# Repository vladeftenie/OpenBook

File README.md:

# OpenBook ESP32-C6 Complete Hardware Guide

## Overview
The OpenBook is an e-reader built around the ESP32-C6 chip. It uses an e-paper screen (like Kindle), has an SD card slot for books, can check room temperature and air quality, and has a battery that lasts a long time. It connects to Wi-Fi and Bluetooth so you can download books and update it.

## Main Parts

### Brain: ESP32-C6-WROOM-1-N8
- **What It Does**: Controls everything in the device
- **Architecture**: RISC-V (Single-Core)
- **Wireless**: Wi-Fi 6, Bluetooth 5 LE
- **Power Needs**: 3.3V
- **How It Talks**: SPI, I²C, UART, GPIO, USB

## Display Details

### E-Paper Screen
- **How It Connects**: SPI (shares wires with SD card)
- **Wires**:
  - Select Wire (EPD_CS): `GPIO 10`
  - Command Wire (EPD_DC): `GPIO 5`
  - Reset Wire: `GPIO 23`
  - Busy Signal: `GPIO 3`
  - Data Wires: shared with SD card
- **Screen Size**: 1404 × 1872 pixels (6.8")

## Memory Options

### SD Card Slot
- **How It Connects**: SPI
- **Wires**:
  - Select Wire (SS_SD): `GPIO 4`
  - Data Out (MOSI): `GPIO 7`
  - Data In (MISO): `GPIO 27`
  - Clock (SCK): `GPIO 6`
- **Space**: Works with cards up to 32GB

### Built-in Flash Memory (64MB)
- **How It Connects**: SPI (shared)
- **Wires**:
  - Select Wire (FLASH_CS): `GPIO 12`
  - Shared: `MOSI`, `MISO`, `SCK`
- **What It Stores**: System files, fonts, and some books
- **Chip Used**: W25Q512JVEIQ (Winbond)

## Power System

### Power Supply
- **Gets Power From**: USB-C (5V)
- **Gives Power At**: 3.3V using a voltage regulator
- **Battery**: 3.7V Li-Po, 2000mAh

### Charging System
- **What It Does**: Charges the Li-Po battery
- **Charging Speed**: 500mA
- **Chip Used**: MCP73831T-2ACI-OT (Microchip)

### Battery Monitor
- **What It Does**: Checks battery level and voltage
- **How It Connects**: I²C
- **Chip Used**: MAX17048G+T10 (Analog Devices)

### Backup Power
- **What It Does**: Keeps critical parts running during battery swaps
- **Part Used**: CPH3225A supercapacitor (Seiko)

## Sensors

### Air Quality Sensor – BME688
- **What It Measures**: Temperature, humidity, air pressure, gas levels
- **How It Connects**: I²C (shares wires with clock)
- **Power Needs**: 3.3V
- **Power Control Wire**: `GPIO 17`

### Clock Chip – DS3231SN
- **What It Does**: Keeps accurate time even when powered off
- **How It Connects**: I²C
- **Wires**:
  - Clock Wire (SCL): `GPIO 20`
  - Data Wire (SDA): `GPIO 19`
  - Alert Wire (INT): `GPIO 8`
  - Timing Wire (32KHz): `GPIO 9`
  - Reset Wire: `GPIO 16`
- **How Accurate**: About 1 minute off per year

## Connecting to Other Things

### USB-C Port
- **What It Does**: Charges the device and transfers data
- **Data Wires**:
  - USB_D-: `GPIO 13`
  - USB_D+: `GPIO 14`
- **Protection**: Has surge protection (USBLC6-2SC6Y chip)

### Expansion Port (Qwiic / Stemma QT)
- **What It Does**: Lets you add other sensors or devices
- **How It Connects**: I²C
- **Power Out**: 3.3V
- **Wires**: Uses the same I²C wires as other parts

## User Buttons
- **Boot Button**: Connected to `GPIO 15` (changes boot mode)
- **Reset Button**: Connected to pin 3 (restarts device)
- **Mode Button**: Connected to `GPIO 23` (changes display modes)

## Protection Features
- Surge protectors on USB and other wires
- Protection against putting batteries in backward
- Static electricity protection

## How Parts Connect

| Pin Number | What It Does | Connects To | More Info |
|------------|--------------|-------------|-----------|
| 3 | RESET | Reset Button | Restarts the whole system |
| 4 | SS_SD | SD Card (pin 2) | Selects the SD card for talking |
| 6 | SCK | SD Card (pin 5) | Clock beat for data timing |
| 7 | MOSI | SD Card (pin 3) | Sends data out to SD card |
| 8 | INT_RTC | Clock Chip (pin 3) | Gets alerts from the clock |
| 9 | 32KHz | Clock Chip (pin 1) | Gets timing signal from clock |
| 13 | USB_D- | USB-C Port (pin 3) | USB negative data wire |
| 14 | USB_D+ | USB-C Port (pin 1) | USB positive data wire |
| 15 | IO/BOOT | Boot Button | Selects startup mode |
| 16 | RTC_RST | Clock Chip (pin 4) | Resets the clock chip |
| 17 | I2C_PW | Air Sensor (pins 6, 8, 2) | Controls power to air sensor |
| 19 | SDA | Multiple devices | Shared data wire for I²C |
| 20 | SCL | Multiple devices | Shared clock wire for I²C |
| 23 | IO/CHANGE | Mode Button | Changes display/device mode |
| 27 | MISO | SD Card (pin 7) | Gets data from SD card |

## How It All Connects

## BOM

| Component | Link | Estimated Price |
|------------|------|----------------|
| R1_PINH1, R2-PINH1, R_BOOT, R_CHARGE, R_CL1, R_RESET | https://componentsearchengine.com/part-view/R0402%201%25%20100%20K%20(RC0402FR-07100KL)/YAGEO | €0.01 (per unit) |
| R1, R1-PINH, R2-PINH, R4, R5, R6, R7, R8, R9, R10 | https://componentsearchengine.com/part-view/R0402%201%25%20100%20K%20(RC0402FR-07100KL)/YAGEO | €0.01 (per unit) |
| C5 | https://componentsearchengine.com/part-view/CC0402MRX5R5BB106/YAGEO | €0.10 |
| EPD_C1, EPD_C2, EPD_C5, EPD_C6, EPD_C7, EPD_C8, EPD_C9, EPD_C10, EPD_C11, EPD_C12 | https://componentsearchengine.com/part-view/CC0402MRX5R5BB106/YAGEO | €0.10 (per unit) |
| R2 | https://componentsearchengine.com/part-view/R0402%201%25%20100%20K%20(RC0402FR-07100KL)/YAGEO | €0.01 |
| R1_BAT | https://componentsearchengine.com/part-view/R0402%201%25%20100%20K%20(RC0402FR-07100KL)/YAGEO | €0.01 |
| U4 | https://www.snapeda.com/api/url_track_click_mouser/?unipart_id=329239&manufacturer=Analog%20Devices&part_name=MAX17048G+T10&search_term=None | €3.80 |
| J2 | https://componentsearchengine.com/part-view/USB4110-GF-A/GCT%20(GLOBAL%20CONNECTOR%20TECHNOLOGY) | €0.95 |
| D1 | https://www.snapeda.com/parts/USBLC6-2SC6Y/STMicroelectronics/view-part/?ref=eda | €0.60 |
| U1 | https://www.snapeda.com/parts/W25Q512JVEIQ/Winbond+Electronics/view-part/?ref=eda | €4.20 |
| D3, D4, D5 | https://www.snapeda.com/api/url_track_click_mouser/?unipart_id=179458&manufacturer=ON%20Semiconductor&part_name=MBR0530&search_term=None | €0.40 (per unit) |
| D6, D8, D9, D10, D11, D12 | https://www.snapeda.com/api/url_track_click_mouser/?unipart_id=5659453&manufacturer=Littelfuse%20Inc.&part_name=PGB1010603MR&search_term=None | €0.30 (per unit) |
| J3 | https://www.digikey.ro/en/models/926710 | €1.05 |
| C1_BAT, C1_BAT1, C1_BAT2, C2_BAT, C5_USB | https://componentsearchengine.com/part-view/CC0402MRX5R5BB106/YAGEO | €0.10 (per unit) |
| C4 | https://componentsearchengine.com/part-view/CC0402MRX5R5BB106/YAGEO | €0.10 |
| R2-USB, R2-USB1 | https://componentsearchengine.com/part-view/R0402%201%25%20100%20K%20(RC0402FR-07100KL)/YAGEO | €0.01 (per unit) |
| C1, C2, C4_USB, C6, C7, C8, C9, C10, C_DELAY | https://componentsearchengine.com/part-view/CC0402MRX5R5BB106/YAGEO | €0.10 (per unit) |
| C3 | https://a360.co/4iZy6AA | €0.12 |
| J4 | https://store.comet.srl.ro/Catalogue/Product/43497/ | €0.35 |
| R_CAPACITOR | https://componentsearchengine.com/part-view/R0402%201%25%20100%20K%20(RC0402FR-07100KL)/YAGEO | €0.01 |
| R2_BAT | https://componentsearchengine.com/part-view/R0402%201%25%20100%20K%20(RC0402FR-07100KL)/YAGEO | €0.01 |
| TP1, TP2, TP3, TP4, TP5, TP6, TP7, TP8, TP9, TP10, TP11, TP12, TP13, TP14, TP15, TP16, TP17 | https://grabcad.com/library/test-points-printed-circuit-board-1 | €0.02 (per unit) |
| U2 | https://www.snapeda.com/parts/ESP32-C6-WROOM-1-N8/Espressif+Systems/view-part/?ref=eda | €4.50 |
| PFMF.050.1 | https://www.mouser.co.uk/ProductDetail/EPCOS-TDK/B72520T0350K062?qs=dEfas%2FXlABIszF52uu7vrg%3D%3D | €0.65 |
| CHG_LED | https://www.snapeda.com/parts/KP-1608SURCK/Kingbright/view-part/?ref=search&t=LED%200603 | €0.15 |
| SJ1 | https://grabcad.com/library/solder-jumpers-1 | €0.05 |
| SENSOR2 | https://www.snapeda.com/parts/BME680/Bosch/view-part/?welcome=home | €10.50 |
| MCP73831 | https://www.digikey.ro/en/products/detail/microchip-technology/MCP73831T-2ACI-OT/964301 | €0.75 |
| J1 | https://componentsearchengine.com/part-view/XC6220A331MR-G/Torex | €1.25 |
| R3 | https://componentsearchengine.com/part-view/R0402%201%25%20100%20K%20(RC0402FR-07100KL)/YAGEO | €0.01 |
| R1_PWRUSB | https://componentsearchengine.com/part-view/R0402%201%25%20100%20K%20(RC0402FR-07100KL)/YAGEO | €0.01 |
| IC4 | https://componentsearchengine.com/part-view/XC6220A331MR-G/Torex | €1.25 |
| L1 | https://eu.mouser.com/ProductDetail/Wurth-Elektronik/744043680?qs=PGXP4M47uW6VkZq%252BkzjrHA%3D%3D | €0.85 |
| IC1 | https://componentsearchengine.com/part-view/BD5229G-TR/ROHM%20Semiconductor | €1.20 |
| BOOT_BUTTON, CHANGE_BUTTON, RESET_BUTTON | https://www.snapeda.com/parts/EVQP7L01P/Panasonic/view-part/?ref=search&t=evqp7l | €0.25 (per unit) |
| C10_SUPERCAP | https://www.snapeda.com/api/url_track_click_mouser/?unipart_id=562593&manufacturer=Seiko%20Instruments&part_name=CPH3225A&search_term=None | €2.50 |
| U3 | https://www.snapeda.com/api/url_track_click_mouser/?unipart_id=99048&manufacturer=Analog%20Devices&part_name=DS3231SN#&search_term=None | €8.95 |
| Q2 | https://componentsearchengine.com/part-view/DMG2305UX-7/Diodes%20Incorporated | €0.55 |
| Q1, Q3 | https://componentsearchengine.com/part-view/SI1308EDL-T1-GE3/Vishay | €0.45 (per unit) |
| D2, D7 | https://eu.mouser.com/ProductDetail/KYOCERA-AVX/SD0805S020S1R0?qs=jCA%252BPfw4LHbpkAoSnwrdjw%3D%3D | €0.30 (per unit) |

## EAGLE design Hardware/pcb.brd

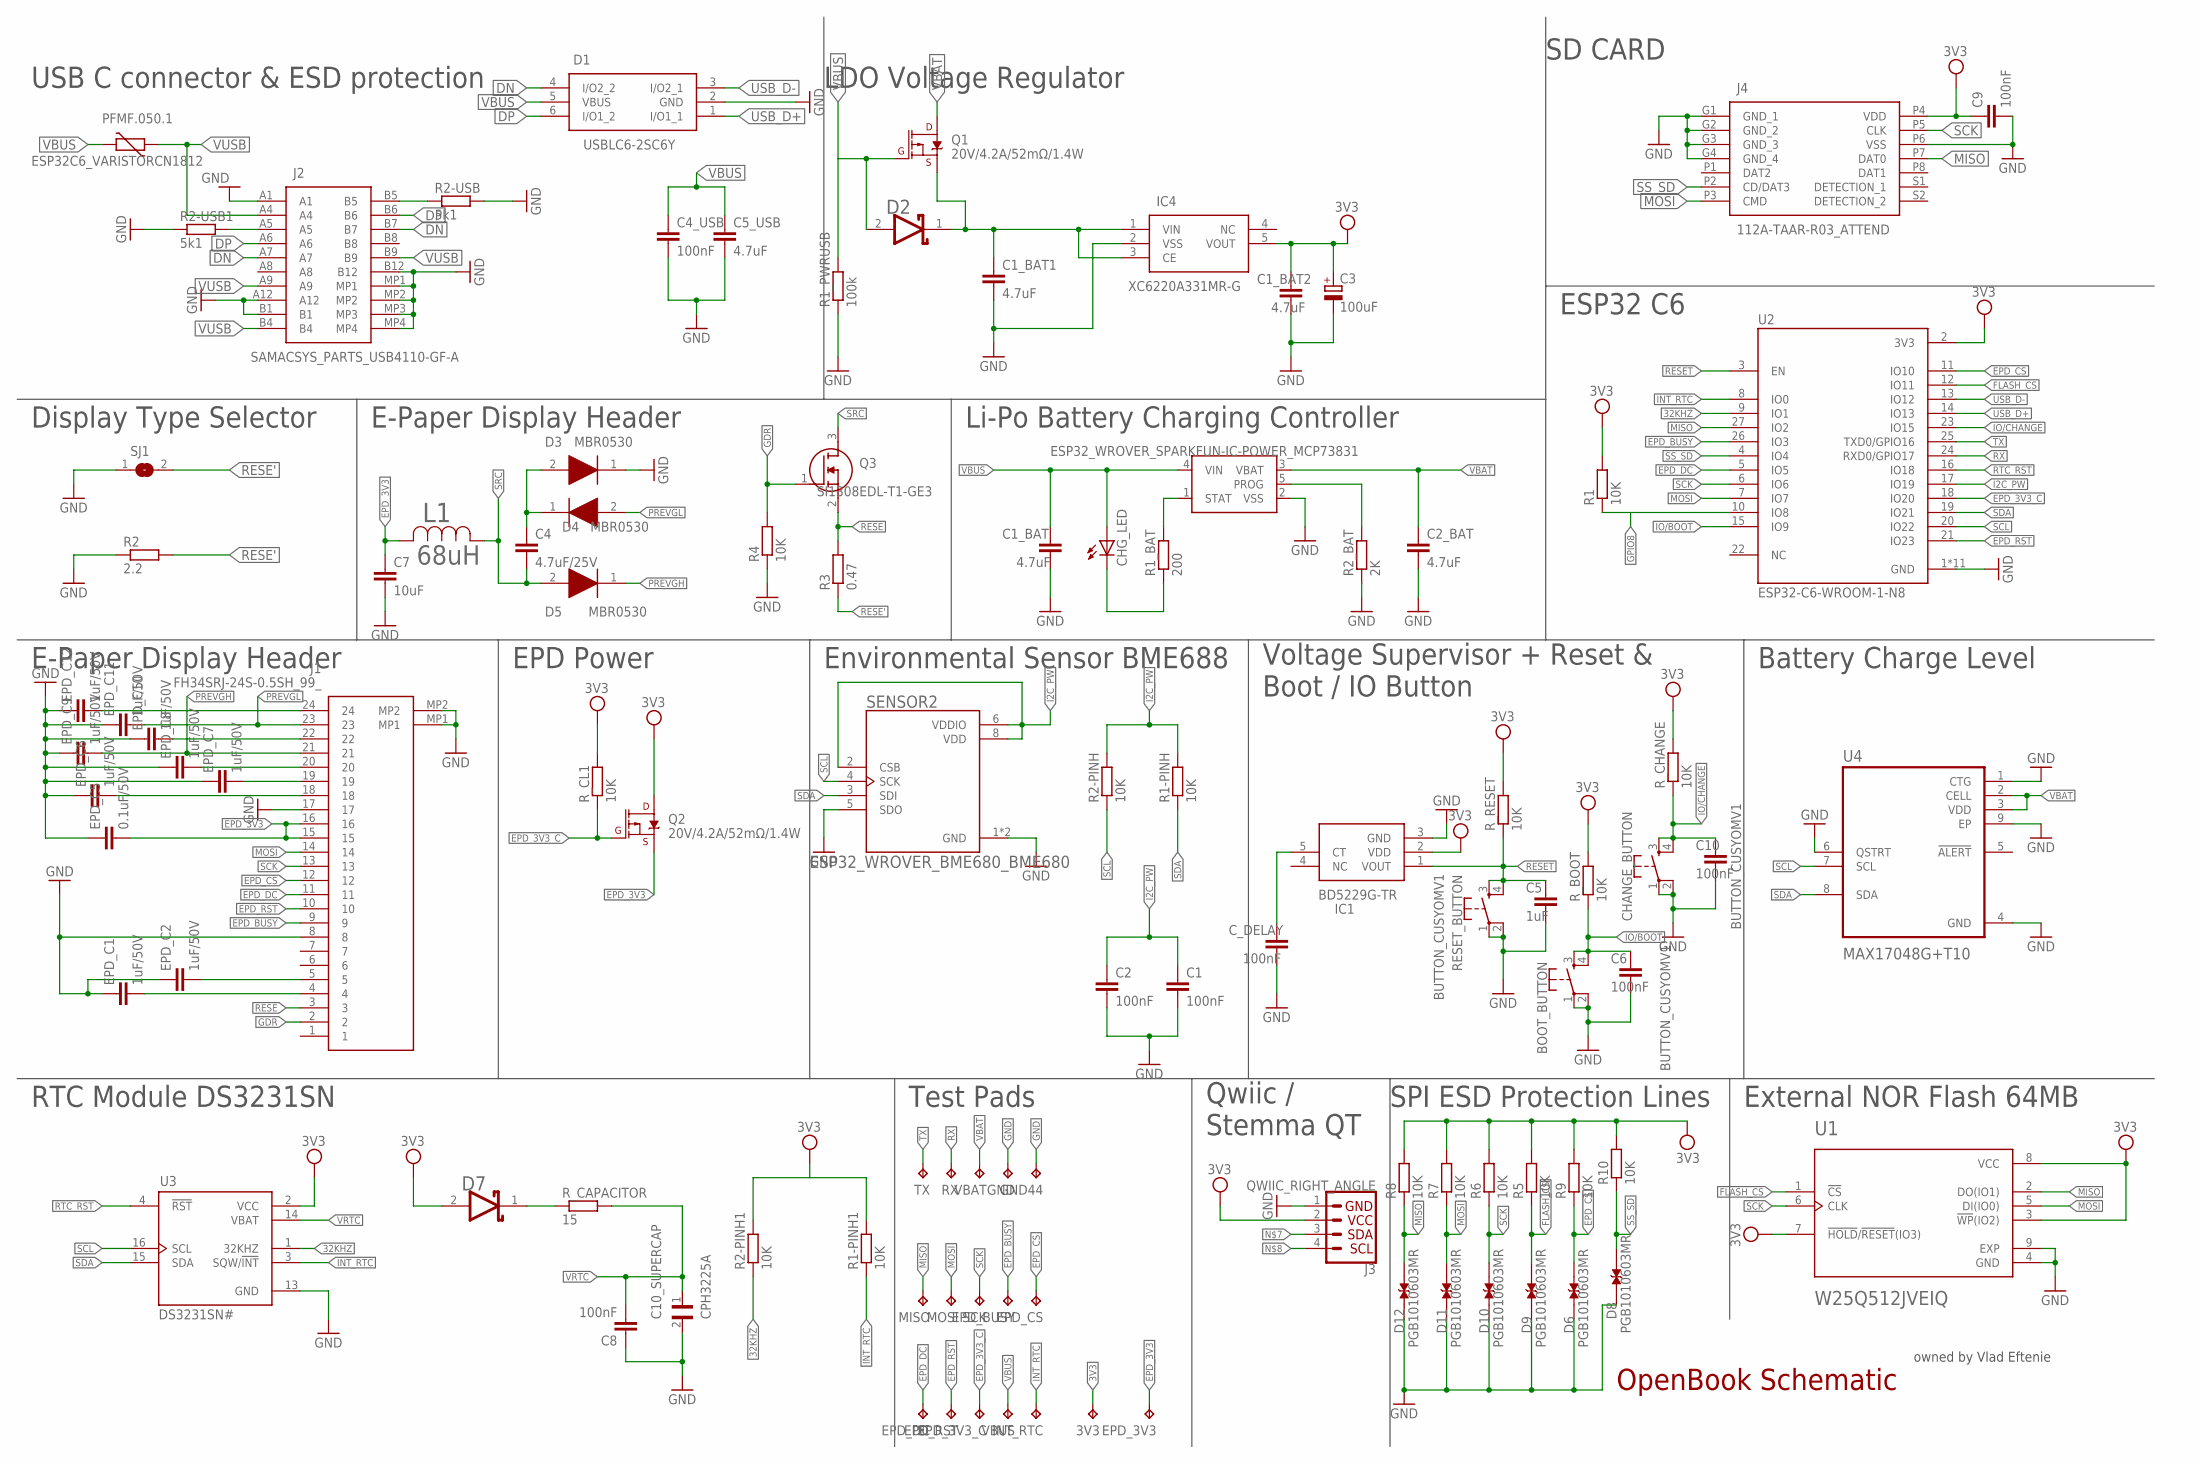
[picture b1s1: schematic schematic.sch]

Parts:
3V3: TPTP20R; TP20R
BOOT_BUTTON: BUTTON_CUSYOMV1; MYBUTTON
C1, C2, C4_USB, C6, C8, C9, C10: 100nF; ESP32_WROVER_EAGLE-LTSPICE_C0402
C1_BAT, C1_BAT1, C1_BAT2, C2_BAT, C5_USB: 4.7uF; ESP32_WROVER_EAGLE-LTSPICE_C0402
C3: 100uF; RCL_CT3528
C4: 4.7uF/25V; ESP32_WROVER_EAGLE-LTSPICE_C0402
C5: 1uF; ESP32_WROVER_EAGLE-LTSPICE_C0402
C7: 10uF; ESP32_WROVER_EAGLE-LTSPICE_C0402
C10_SUPERCAP: CPH3225A; CAPCP3225X100N
CHANGE_BUTTON: BUTTON_CUSYOMV1; MYBUTTON
CHG_LED: ADAFRUIT_LEDCHIP-LED0603; ADAFRUIT_CHIP-LED0603
C_DELAY: 100nF; ESP32_WROVER_EAGLE-LTSPICE_C0402
D1: USBLC6-2SC6Y; SOT95P280X145-6N
D2, D7: ESP32_WROVER_AVX---SD0805S020S1R0_AVX_SD0805S020S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; ESP32_WROVER_AVX---SD0805S020S1R0_AVX_SD0805S020S1R0_0
D3, D4, D5: MBR0530; SOD3716X135N
D6, D8, D9, D10, D11, D12: PGB1010603MR; DIOC1608X36N
EPD_3V3, EPD_3V3_C: TPTP20R; TP20R
EPD_BUSY: TPTP20R; TP20R
EPD_C1, EPD_C2, EPD_C6, EPD_C7, EPD_C8, EPD_C9, EPD_C10, EPD_C11, EPD_C12: 1uF/50V; ESP32_WROVER_EAGLE-LTSPICE_C0402
EPD_C5: 0.1uF/50V; ESP32_WROVER_EAGLE-LTSPICE_C0402
EPD_CS: TPTP20R; TP20R
EPD_DC: TPTP20R; TP20R
EPD_RST: TPTP20R; TP20R
GND, GND44: TPTP20R; TP20R
IC1: BD5229G-TR; SOT95P280X125-5N
IC4: XC6220A331MR-G; SOT95P280X120-5N
INT_RTC: TPTP20R; TP20R
J1: FH34SRJ-24S-0.5SH_99_; FH34SRJ24S05SH99
J2: SAMACSYS_PARTS_USB4110-GF-A; SAMACSYS_PARTS_USB4110GFA
J3: QWIIC_RIGHT_ANGLE; JST04_1MM_RA
J4: 112A-TAAR-R03_ATTEND; 112ATAARR03ATTEND
L1: 68uH; IND_4828-WE-TPC_WRE
MCP73831: ESP32_WROVER_SPARKFUN-IC-POWER_MCP73831; ESP32_WROVER_SPARKFUN-IC-POWER_SOT23-5
MISO: TPTP20R; TP20R
MOSI: TPTP20R; TP20R
PFMF.050.1: ESP32C6_VARISTORCN1812; ESP32C6_VARISTOR_CT/CN1812
Q1, Q2: 20V/4.2A/52mΩ/1.4W; ESP32_WROVER_SPARKFUN-DISCRETESEMI_SOT23-3
Q3: SI1308EDL-T1-GE3; SOT65P210X110-3N
R1, R1-PINH, R1-PINH1, R2-PINH, R2-PINH1, R4, R5, R6, R7, R8, R9, R10: 10K; ESP32_WROVER_EAGLE-LTSPICE_R0402
R1_BAT: 200; ESP32_WROVER_EAGLE-LTSPICE_R0402
R1_PWRUSB: 100k; ESP32_WROVER_EAGLE-LTSPICE_R0402
R2: 2.2; ESP32_WROVER_EAGLE-LTSPICE_R0402
R2-USB, R2-USB1: 5k1; ESP32_WROVER_EAGLE-LTSPICE_R0402
R2_BAT: 2K; ESP32_WROVER_EAGLE-LTSPICE_R0402
R3: 0.47; ESP32_WROVER_EAGLE-LTSPICE_R0402
RESET_BUTTON: BUTTON_CUSYOMV1; MYBUTTON
RX: TPTP20R; TP20R
R_BOOT: 10K; ESP32_WROVER_EAGLE-LTSPICE_R0402
R_CAPACITOR: 15; ESP32_WROVER_EAGLE-LTSPICE_R0402
R_CHANGE: 10K; ESP32_WROVER_EAGLE-LTSPICE_R0402
R_CL1: 10K; ESP32_WROVER_EAGLE-LTSPICE_R0402
R_RESET: 10K; ESP32_WROVER_EAGLE-LTSPICE_R0402
SCK: TPTP20R; TP20R
SENSOR2: ESP32_WROVER_BME680_BME680; ESP32_WROVER_BME680_PSON80P300X300X100-8N
SJ1: SJ
TX: TPTP20R; TP20R
U1: W25Q512JVEIQ; SON127P600X800X80-9N
U2: ESP32-C6-WROOM-1-N8; XCVR_ESP32-C6-WROOM-1-N8
U3: DS3231SN#; SOIC127P1032X265-16N
U4: MAX17048G+T10; SON50P200X200X80-9N
VBAT: TPTP20R; TP20R
VBUS: TPTP20R; TP20R

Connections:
3V3: 3V3.TP, C1_BAT2.1, C3.+, C9.1, D7.2 (ANODE), IC1.2 (VDD), IC4.5 (VOUT), J3.2, J4.P4 (VDD), Q2.3 (D), R1.2, R5.2, R6.2, R7.2, R8.2, R9.2, R10.2, R_BOOT.2, R_CHANGE.2, R_CL1.2, R_RESET.2, U1.3 (!WP!(IO2)), U1.7 (!HOLD!/!RESET!(IO3)), U1.8 (VCC), U2.2 (3V3), U3.2 (VCC)
32KHZ: R2-PINH1.1, U2.9 (IO1), U3.1 (32KHZ)
DN: D1.4 (I/O2_2), J2.A7, J2.B7
DP: D1.6 (I/O1_2), J2.A6, J2.B6
EPD_3V3: C7.1, EPD_3V3.TP, EPD_C5.2, J1.15, J1.16, L1.2, Q2.2 (S)
EPD_3V3_C: EPD_3V3_C.TP, Q2.1 (G), R_CL1.1, U2.18 (IO20)
EPD_BUSY: EPD_BUSY.TP, J1.9, U2.26 (IO3)
EPD_CS: D6.2, EPD_CS.TP, J1.12, R9.1, U2.11 (IO10)
EPD_DC: EPD_DC.TP, J1.11, U2.5 (IO5)
EPD_RST: EPD_RST.TP, J1.10, U2.21 (IO23)
FLASH_CS: D9.2, R5.1, U1.1 (!CS), U2.12 (IO11)
GDR: J1.2, Q3.1 (G), R4.2
GND: BOOT_BUTTON.1, BOOT_BUTTON.2, C1.2, C1_BAT.2, C1_BAT1.2, C1_BAT2.2, C2.2, C2_BAT.2, C3.-, C4_USB.2, C5.2, C5_USB.2, C6.2, C7.2, C8.1, C9.2, C10.2, C10_SUPERCAP.2, CHANGE_BUTTON.1, CHANGE_BUTTON.2, C_DELAY.2, D1.2 (GND), D3.1 (K), D6.1, D8.1, D9.1, D10.1, D11.1, D12.1, EPD_C1.1, EPD_C2.1, EPD_C5.1, EPD_C6.1, EPD_C7.1, EPD_C8.1, EPD_C9.1, EPD_C10.1, EPD_C11.1, EPD_C12.1, GND.TP, GND44.TP, IC1.3 (GND), IC4.2 (VSS), J1.8, J1.17, J1.MP1, J1.MP2, J2.A1, J2.A12, J2.B1, J2.B12, J2.MP1, J2.MP2, J2.MP3, J2.MP4, J3.1, J4.G1 (GND_1), J4.G2 (GND_2), J4.G3 (GND_3), J4.G4 (GND_4), J4.P6 (VSS), MCP73831.2 (VSS), R1_PWRUSB.1, R2.1, R2-USB.2, R2-USB1.1, R2_BAT.1, R4.1, RESET_BUTTON.1, RESET_BUTTON.2, SENSOR2.1 (GND), SENSOR2.5 (SDO), SENSOR2.7 (GND), SJ1.1, U1.4 (GND), U1.9 (EXP), U2.1 (GND), U2.28 (GND), U2.29_1 (GND), U2.29_2 (GND), U2.29_3 (GND), U2.29_4 (GND), U2.29_5 (GND), U2.29_6 (GND), U2.29_7 (GND), U2.29_8 (GND), U2.29_9 (GND), U3.13 (GND), U4.1 (CTG), U4.4 (GND), U4.6 (QSTRT), U4.9 (EP)
I2C_PW: C1.1, C2.1, R1-PINH.2, R2-PINH.2, SENSOR2.2 (CSB), SENSOR2.6 (VDDIO), SENSOR2.8 (VDD), U2.17 (IO19)
INT_RTC: INT_RTC.TP, R1-PINH1.1, U2.8 (IO0), U3.3 (SQW/!INT)
IO/BOOT: BOOT_BUTTON.3, BOOT_BUTTON.4, C6.1, R_BOOT.1, U2.15 (IO9)
IO/CHANGE: C10.1, CHANGE_BUTTON.3, CHANGE_BUTTON.4, R_CHANGE.1, U2.23 (IO15)
MISO: D12.2, J4.P7 (DAT0), MISO.TP, R8.1, U1.2 (DO(IO1)), U2.27 (IO2)
MOSI: D11.2, J1.14, J4.P3 (CMD), MOSI.TP, R7.1, U1.5 (DI(IO0)), U2.7 (IO7)
unnamed: J2.A5, R2-USB1.2
unnamed: J2.B5, R2-USB.1
unnamed: D2.2 (ANODE), Q1.1 (G)
unnamed: R1.1, U2.10 (IO8)
unnamed: C1_BAT1.1, D2.1 (CATHODE), IC4.1 (VIN), IC4.3 (CE), Q1.2 (S)
unnamed: C4.1, D3.2 (A), D4.1 (K)
unnamed: MCP73831.1 (STAT), R1_BAT.2
unnamed: MCP73831.5 (PROG), R2_BAT.2
unnamed: C_DELAY.1, IC1.5 (CT)
unnamed: EPD_C12.2, J1.24
unnamed: R1-PINH1.2, R2-PINH1.2
unnamed: CHG_LED.C, R1_BAT.1
unnamed: EPD_C10.2, J1.22
unnamed: D7.1 (CATHODE), R_CAPACITOR.1
unnamed: EPD_C8.2, J1.20
unnamed: EPD_C7.2, J1.19
unnamed: EPD_C6.2, J1.18
unnamed: EPD_C1.2, J1.4
unnamed: EPD_C2.2, J1.5
PREVGH: D5.1 (K), EPD_C9.2, J1.21
PREVGL: D4.2 (A), EPD_C11.2, J1.23
RESE: J1.3, Q3.2 (S), R3.2
RESE': R2.2, R3.1, SJ1.2
RESET: C5.1, IC1.1 (VOUT), RESET_BUTTON.3, RESET_BUTTON.4, R_RESET.1, U2.3 (EN)
RTC_RST: U2.16 (IO18), U3.4 (!RST)
RX: RX.TP, U2.24 (RXD0/GPIO17)
SCK: D10.2, J1.13, J4.P5 (CLK), R6.1, SCK.TP, U1.6 (CLK), U2.6 (IO6)
SCL: R2-PINH.1, SENSOR2.4 (SCK), U2.20 (IO22), U3.16 (SCL), U4.7 (SCL)
SDA: R1-PINH.1, SENSOR2.3 (SDI), U2.19 (IO21), U3.15 (SDA), U4.8 (SDA)
SRC: C4.2, D5.2 (A), L1.1, Q3.3 (D)
SS_SD: D8.2, J4.P2 (CD/DAT3), R10.1, U2.4 (IO4)
TX: TX.TP, U2.25 (TXD0/GPIO16)
USB_D+: D1.1 (I/O1_1), U2.14 (IO13)
USB_D-: D1.3 (I/O2_1), U2.13 (IO12)
VBAT: C2_BAT.1, MCP73831.3 (VBAT), Q1.3 (D), U4.2 (CELL), U4.3 (VDD), VBAT.TP
VBUS: C1_BAT.1, C4_USB.1, C5_USB.1, CHG_LED.A, D1.5 (VBUS), MCP73831.4 (VIN), PFMF.050.1.2, R1_PWRUSB.2, VBUS.TP
VRTC: C8.2, C10_SUPERCAP.1, R_CAPACITOR.2, U3.14 (VBAT)
VUSB: J2.A4, J2.A9, J2.B4, J2.B9, PFMF.050.1.1

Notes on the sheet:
owned by Vlad Eftenie
USB C connector & ESD protection
LDO Voltage Regulator
SD CARD
Display Type Selector
E-Paper Display Header
Li-Po Battery Charging Controller
ESP32 C6
EPD Power
Environmental Sensor BME688
Voltage Supervisor + Reset & Boot / IO Button
Battery Charge Level
RTC Module DS3231SN
Test Pads
Qwiic / Stemma QT
SPI ESD Protection Lines
OpenBook Schematic
External NOR Flash 64MB

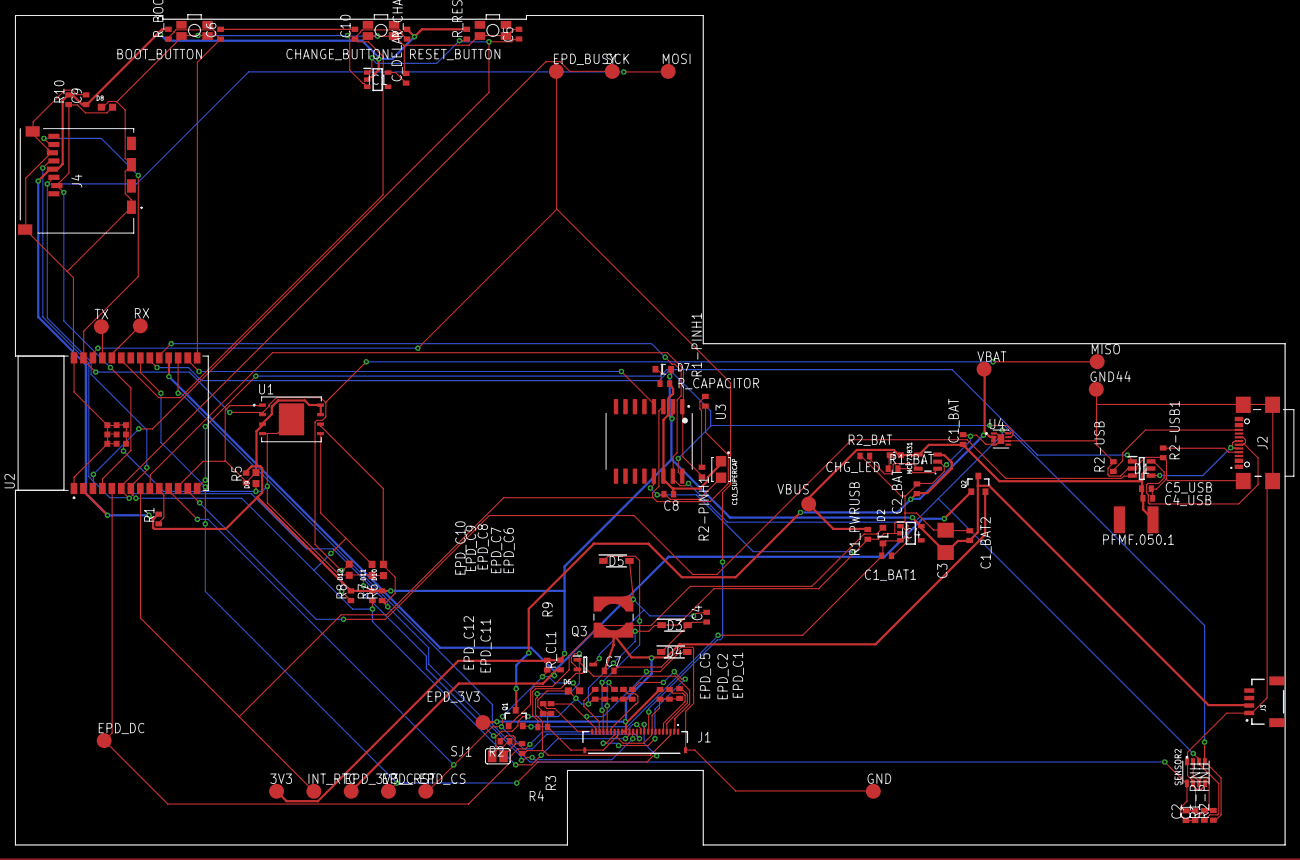
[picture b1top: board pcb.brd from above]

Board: 2 copper layers, 170.2 x 111.2 mm, 103 parts (0 on the bottom side), 57 nets.

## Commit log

2025-04-06 project
2025-04-06 Create LICENSE
2025-04-14 issues resolved

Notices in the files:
parts and their libraries:
COPYRIGHT: Copyright (C) 2024 Ultra Librarian. All rights reserved.
